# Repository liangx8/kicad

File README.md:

#content

  * esc ESC project
  * lib component package

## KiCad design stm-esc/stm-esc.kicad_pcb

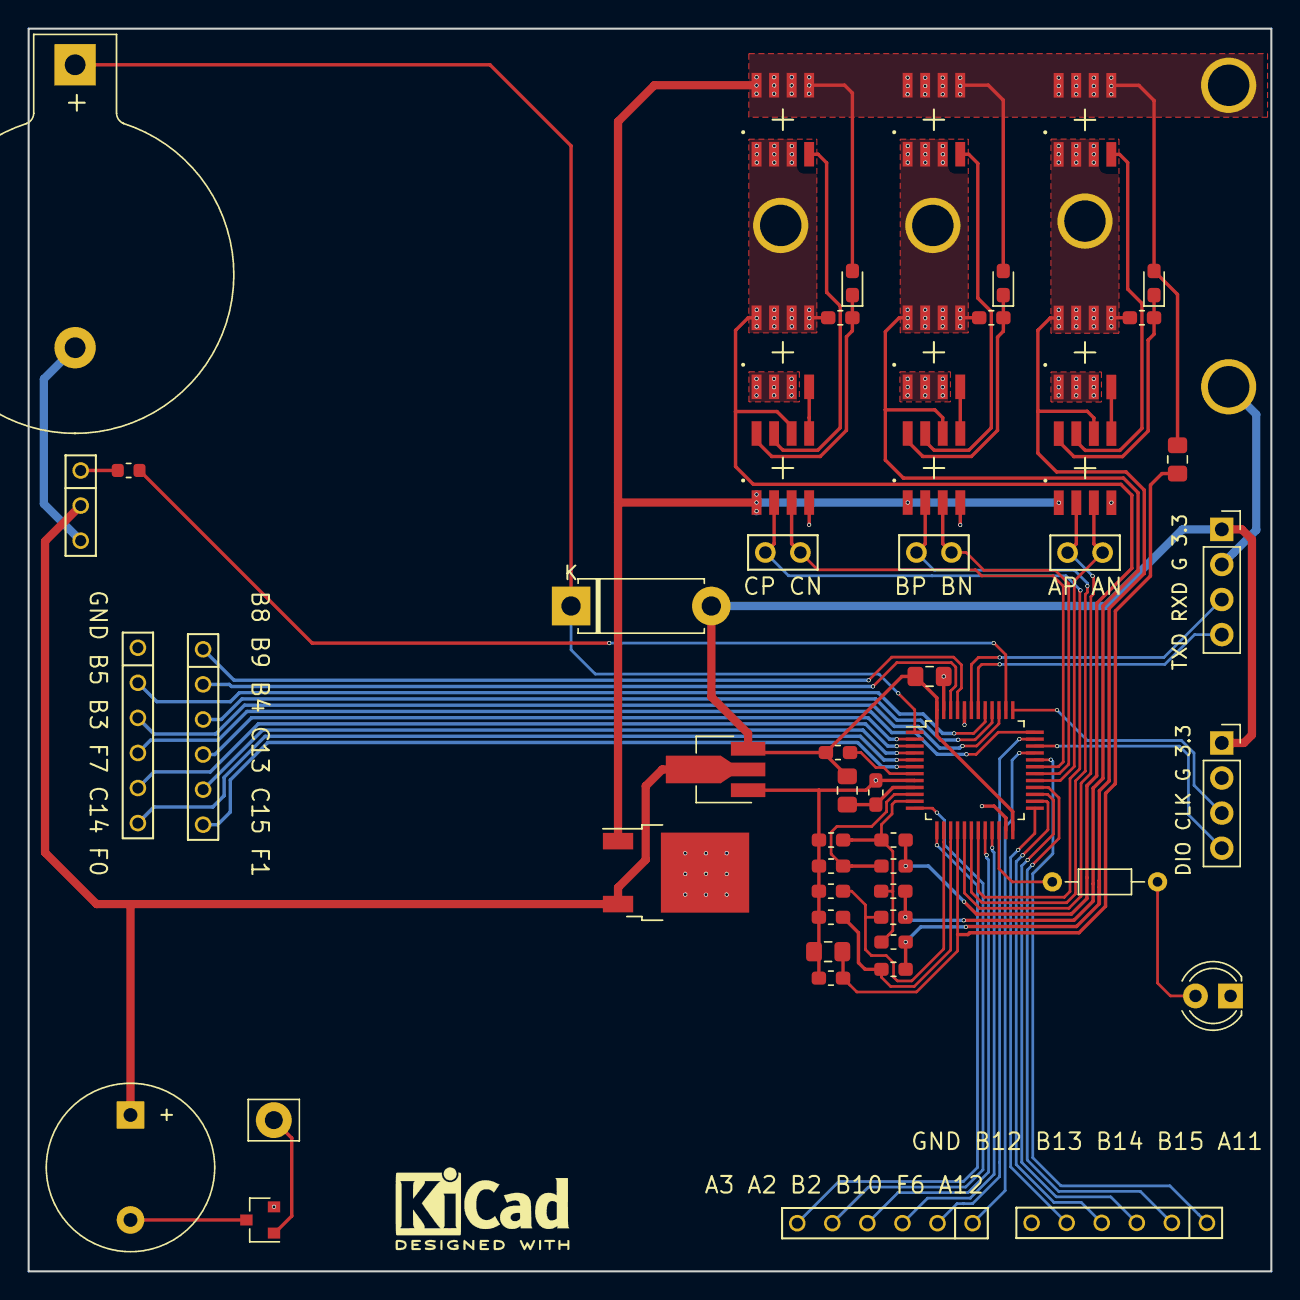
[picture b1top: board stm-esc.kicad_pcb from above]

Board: 2 copper layers, 90.0 x 90.0 mm, 58 parts (0 on the bottom side), 62 nets.

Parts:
BT1: Battery_Cell; BatteryHolder_Keystone_103_1x20mm
BZ1: Buzzer; Buzzer_12x9.5RM7.6
C1, C4: C; C_0603_1608Metric_Pad1.05x0.95mm_HandSolder
C2: C; C_0805_2012Metric_Pad1.15x1.40mm_HandSolder
C3: C; C_0603_1608Metric
C5: Ca; C_0603_1608Metric_Pad1.05x0.95mm_HandSolder
C6: Cc; C_0603_1608Metric_Pad1.05x0.95mm_HandSolder
C7: Cb; C_0603_1608Metric_Pad1.05x0.95mm_HandSolder
D1: D; D_5W_P10.16mm_Horizontal
D2: LED; LED_D4.0mm
D3: Da; D_0603_1608Metric_Pad1.05x0.95mm_HandSolder
D4: Dc; D_0603_1608Metric_Pad1.05x0.95mm_HandSolder
D5: Db; D_0603_1608Metric_Pad1.05x0.95mm_HandSolder
J1: A3 A2 B2 B10 F6 A12; conn-6x2.54mm
J2: GND B12 B13 B14 B15 A11; conn-6x2.54mm
J3, J4: Conn_01x06; conn-6x2.54mm
J5: Conn_01x01; Pin_D1.3mm_L10.0mm_W3.5mm_Flat
J6: DIO CLK G 3.3; PinSocket_1x04_P2.54mm_Vertical
J7: TXD RXD G 3.3; PinSocket_1x04_P2.54mm_Vertical
J8, J9, J14, J15, J16: Conn_01x01; HOLE-R1.5MM
J10: Conn_01x03; conn-3x2.54mm
J11: CP CN; SIP-2xP2.54mm
J12: BP BN; SIP-2xP2.54mm
J13: AP AN; SIP-2xP2.54mm
Q1: 2N7002; SOT-23
Q2, Q3, Q4, Q5, Q6, Q7: nfet; SOIC-8
R1, R13: 1k; R_0603_1608Metric_Pad1.05x0.95mm_HandSolder
R2: 1R; R_0805_2012Metric_Pad1.15x1.40mm_HandSolder
R3: 1K; R_Axial_DIN0204_L3.6mm_D1.6mm_P7.62mm_Horizontal
R4, R5: 2K; R_0805_2012Metric_Pad1.15x1.40mm_HandSolder
R6, R8, R10, R12, R14, R15: 20k; R_0603_1608Metric_Pad1.05x0.95mm_HandSolder
R7, R9, R11: 3k; R_0603_1608Metric_Pad1.05x0.95mm_HandSolder
U1: STM32F051C8Tx; LQFP-48_7x7mm_P0.5mm
U2: KA78M05_TO252; TO-252-2
U3: REGULAR-7133-1; SOT-89-3_Handsoldering
U4, U5, U6: IR2103; SOIC-8

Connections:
+3V3: C2.2, D1.2, J6.1, J7.1, R1.2, R2.1, U1.24, U1.48, U3.3
+5V: BZ1.1, J10.2, U2.3, U3.2
/LED: R3.2, U1.22
/PA2: J1.5, U1.12
/PA3: J1.6, U1.13
/PA11: J2.1, U1.32
/PA12: J1.1, U1.33
/PB2: J1.4, U1.20
/PB3: J3.3, U1.39
/PB4: J4.3, U1.40
/PB5: J3.2, U1.41
/PB8: J4.1, U1.45
/PB9: J4.2, U1.46
/PB10: J1.3, U1.21
/PB12: J2.5, U1.25
/PB13: J2.4, U1.26
/PB14: J2.3, U1.27
/PB15: J2.2, U1.28
/PC13: J4.4, U1.2
/PC14: J3.5, U1.3
/PC15: J4.5, U1.4
/PF0: J3.6, U1.5
/PF1: J4.6, U1.6
/PF6: J1.2, U1.35
/PF7: J3.4, U1.36
/Vdda: C1.2, R2.2, U1.9
/bridge a/AOUT: C5.2, J14.1, Q2.1, Q2.2, Q2.3, Q3.5, Q3.6, Q3.7, Q3.8, R10.1, R12.1, U4.6
/bridge b/BOUT: C7.2, J16.1, Q6.1, Q6.2, Q6.3, Q7.5, Q7.6, Q7.7, Q7.8, R8.1, R14.1, U6.6
/bridge c/COUT: C6.2, J15.1, Q4.1, Q4.2, Q4.3, Q5.5, Q5.6, Q5.7, Q5.8, R6.1, R15.1, U5.6
AN: J13.1, U1.29, U4.3
AP: J13.2, U1.17, U4.2
BN: J12.1, U1.30, U6.3
BP: J12.2, U1.18, U6.2
CN: J11.1, U1.31, U5.3
CP: J11.2, U1.19, U5.2
Fa: R10.2, R11.1, U1.15
Fabc: R12.2, R13.1, R14.2, R15.2, U1.11
Fb: R8.2, R9.1, U1.14
Fc: R6.2, R7.1, U1.10
GND: BT1.2, C1.1, C2.1, C4.2, D2.1, J2.6, J3.1, J6.2, J7.2, J9.1, J10.3, Q1.2, Q3.1, Q3.2, Q3.3, Q5.1, Q5.2, Q5.3, Q7.1, Q7.2, Q7.3, R5.2, R7.2, R9.2, R11.2, R13.2, U1.8, U1.23, U1.44, U1.47, U2.2, U3.1, U4.4, U5.4, U6.4
unnamed: BT1.1, D1.1, U1.1
unnamed: BZ1.2, Q1.3
unnamed: C3.1, J10.1
unnamed: C5.1, D3.1, U4.8
unnamed: C6.1, D4.1, U5.8
unnamed: C7.1, D5.1, U6.8
unnamed: D2.2, R3.1
unnamed: J5.1, Q1.1
unnamed: Q2.4, U4.7
unnamed: Q3.4, U4.5
unnamed: Q4.4, U5.7
unnamed: Q5.4, U5.5
unnamed: Q6.4, U6.7
unnamed: Q7.4, U6.5
unnamed: R1.1, U1.7
RCP: C3.2, U1.38
RXD: J7.3, U1.43
SWCLK: J6.3, U1.37
SWDIO: J6.4, U1.34
TXD: J7.4, U1.42
VCC: D3.2, D4.2, D5.2, J8.1, Q2.5, Q2.6, Q2.7, Q2.8, Q4.5, Q4.6, Q4.7, Q4.8, Q6.5, Q6.6, Q6.7, Q6.8, R4.1, U2.1, U4.1, U5.1, U6.1
V_SAMPLE: C4.1, R4.2, R5.1, U1.16

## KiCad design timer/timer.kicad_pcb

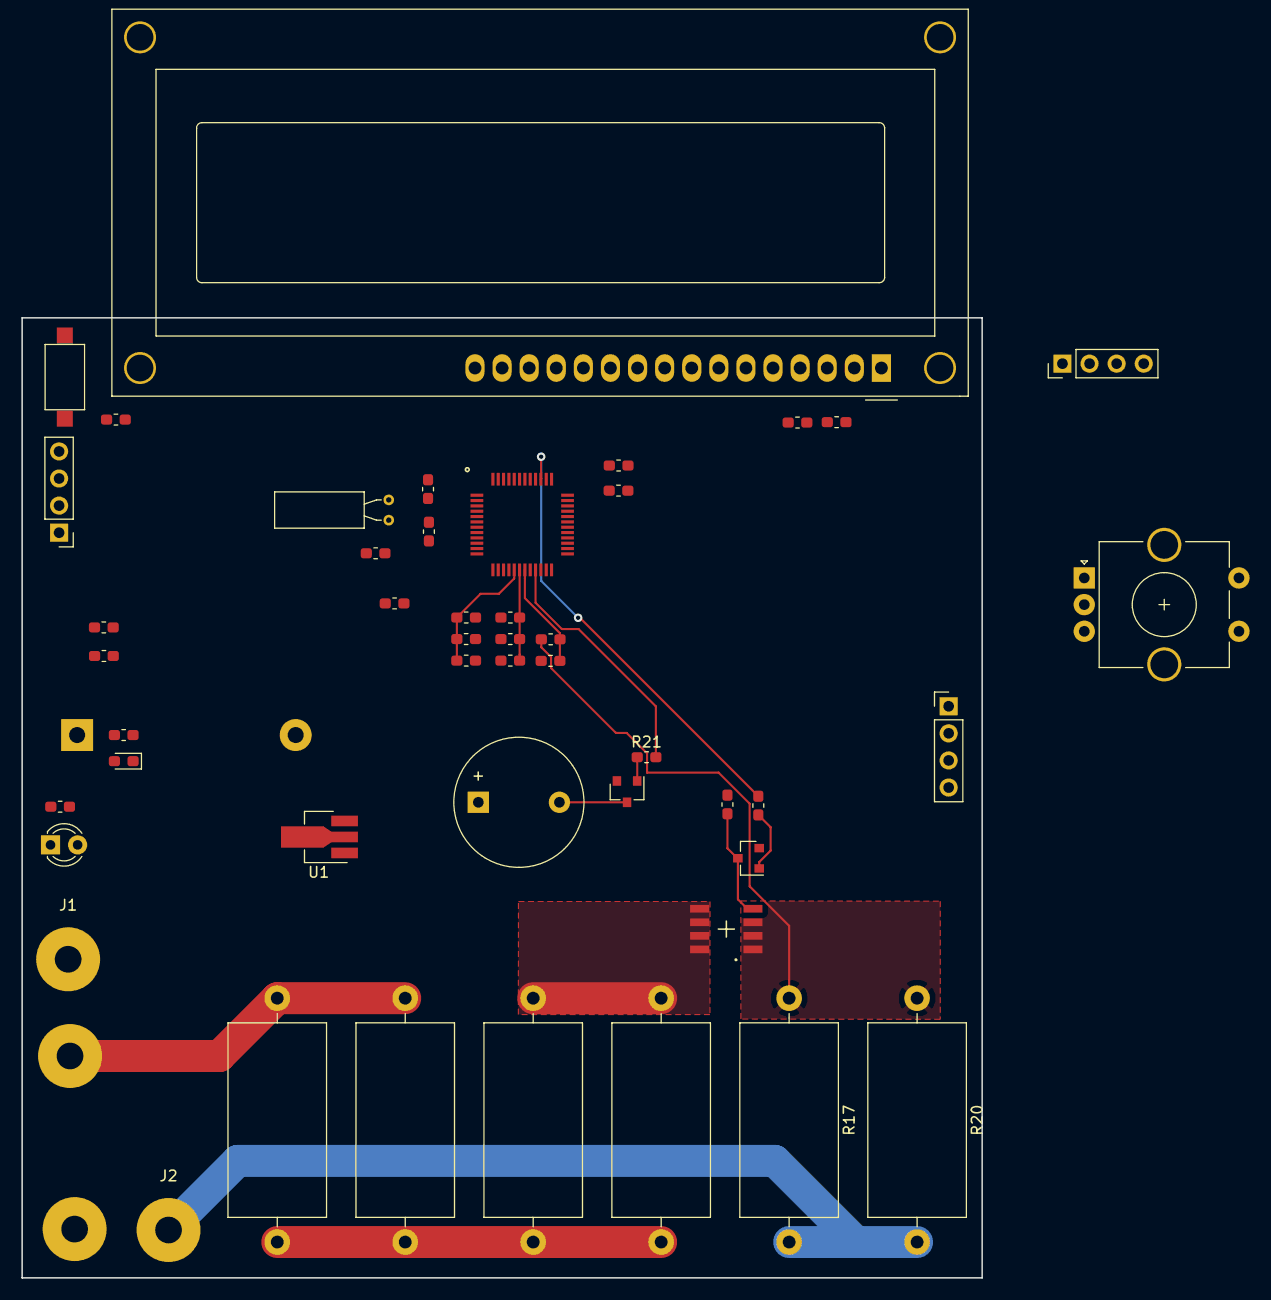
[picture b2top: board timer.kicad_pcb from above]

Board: 2 copper layers, 90.0 x 90.0 mm, 50 parts (1 on the bottom side), 40 nets.

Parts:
BZ1: Buzzer; Buzzer_12x9.5RM7.6
C1, C2: 20p; C_0603_1608Metric_Pad1.05x0.95mm_HandSolder
C3, C4, C5: Cpwr; C_0603_1608Metric_Pad1.05x0.95mm_HandSolder
C6: Calg; C_0603_1608Metric_Pad1.05x0.95mm_HandSolder
C7: Cvs; C_0603_1608Metric_Pad1.05x0.95mm_HandSolder
C8: Cbs; C_0603_1608Metric_Pad1.05x0.95mm_HandSolder
C9: Cis; C_0603_1608Metric_Pad1.05x0.95mm_HandSolder
D1: LED; LED_D3.0mm
D2: D; D_0603_1608Metric_Pad1.05x0.95mm_HandSolder
DS1: WC1602A
J1, J2, J7: Conn_01x01; SolderWirePad_1x01_Drill2.5mm
J3, J4, J5: Conn_01x04; PinHeader_1x04_P2.54mm_Vertical
J6: GND/B-; SolderWirePad_1x01_Drill2.5mm
J8: Conn_01x02; BatteryHolder_Keystone_104_1x23mm
Q1: Q_NPN_BEC; SOT-23
Q2: 2N7002; SOT-23
Q3: nfet; SOIC-8
R1, R2: R; R_0603_1608Metric_Pad1.05x0.95mm_HandSolder
R3: 3k; R_0603_1608Metric_Pad1.05x0.95mm_HandSolder
R4, R5, R12, R13, R21: 1k; R_0603_1608Metric_Pad1.05x0.95mm_HandSolder
R6, R7, R10, R11: 20K; R_0603_1608Metric_Pad1.05x0.95mm_HandSolder
R8: 47k; R_0603_1608Metric_Pad1.05x0.95mm_HandSolder
R9: 4.7k; R_0603_1608Metric_Pad1.05x0.95mm_HandSolder
R14: 10k; R_0603_1608Metric_Pad1.05x0.95mm_HandSolder
R15, R16, R17, R18, R19, R20: 0.1r; R_Axial_DIN0918_L18.0mm_D9.0mm_P22.86mm_Horizontal
SW1: Rotary_Encoder_Switch; RotaryEncoder_Alps_EC11E-Switch_Vertical_H20mm_CircularMoun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
SW2: SW_DIP_x01; SW_SPST_CK_RS282G05A3
U1: REGULAR-7133-1; SOT-89-3_Handsoldering
U2: STM32F103C8Tx; QFP_48_P0.5_W0.3
Y1: Crystal; Crystal_C38-LF_D3.0mm_L8.0mm_Horizontal

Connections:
+1V5: J8.1, R3.1, U2.1
+3V3: C3.1, C4.1, C5.1, C6.1, D2.2, DS1.2, J3.1, J4.1, J5.1, R2.2, R4.2, R5.2, R8.2, U1.3, U2.9, U2.24, U2.36, U2.48
/RESET: R2.1, SW2.2, U2.7
/RXD: J3.4, U2.31
/SWCLK: J4.4, U2.37
/SWDIO: J4.3, U2.34
/TXD: J3.3, U2.30
B+: J7.1, R10.1, R15.1, R18.1
Beep: R21.2, U2.21
Discharge: R12.2, U2.39
GND: C1.2, C2.1, C3.2, C4.2, C5.2, C6.2, C7.2, C8.2, C9.2, DS1.1, J2.1, J3.2, J4.2, J5.2, J6.1, J8.2, Q1.2, Q2.2, R1.2, R7.2, R9.1, R11.2, R17.2, R20.2, SW1.C, SW1.S2, SW2.1, U1.1, U2.8, U2.23, U2.35, U2.44, U2.47
IIC_SCL: J5.3, R4.1, U2.42
IIC_SDA: J5.4, R5.1, U2.43
Isample: C9.1, R14.2, U2.19
unnamed: BZ1.2, Q2.3
unnamed: C1.1, U2.3, Y1.1
unnamed: C2.2, U2.4, Y1.2
unnamed: D1.1, R1.1
unnamed: D1.2, U2.46
unnamed: D2.1, R3.2
unnamed: DS1.3, R8.1, R9.2
unnamed: DS1.4, U2.14
unnamed: DS1.5, U2.15
unnamed: DS1.6, U2.16
unnamed: DS1.11, U2.10
unnamed: DS1.12, U2.11
unnamed: DS1.13, U2.12
unnamed: DS1.14, U2.13
unnamed: Q1.1, R12.1
unnamed: Q1.3, Q3.4, R13.2
unnamed: Q2.1, R21.1
unnamed: Q3.1, Q3.2, Q3.3, R14.1, R17.1, R20.1
unnamed: Q3.5, Q3.6, Q3.7, Q3.8, R16.2, R19.2
unnamed: R15.2, R16.1, R18.2, R19.1
unnamed: SW1.A, U2.40
unnamed: SW1.B, U2.41
unnamed: SW1.S1, U2.45
VCC: BZ1.1, J1.1, R6.1, R13.1, U1.2
Vdd_sample: C7.1, R6.2, R7.1, U2.18
Vsample: C8.1, R10.2, R11.1, U2.17

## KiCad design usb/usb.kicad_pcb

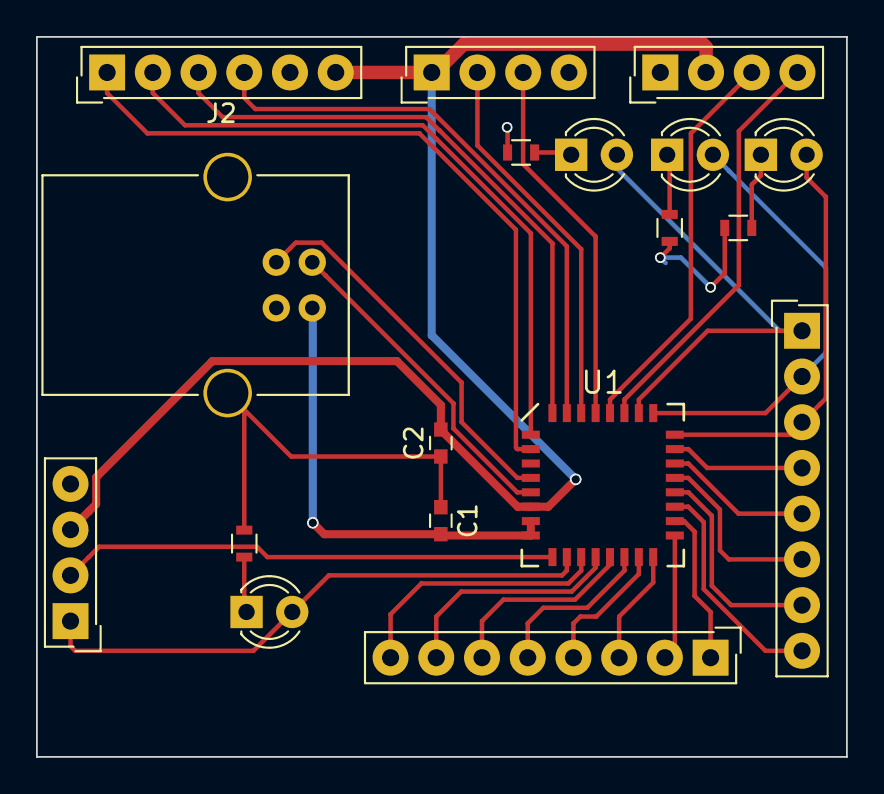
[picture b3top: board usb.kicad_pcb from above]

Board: 2 copper layers, 45.0 x 40.0 mm, 18 parts (0 on the bottom side), 35 nets.

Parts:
C1, C2: 4.7uF; C_0603
D1, D2, D3, D4: LED; LED_D3.0mm
J1: USB_B
J2: SPI; SL-106-X-XX_1x06
J3: C2 interface; SL-104-X-XX_1x04
J4: UART; SL-104-X-XX_1x04
J5: TWI; SL-104-X-XX_1x04
J6: GPIO1; SL-108-X-XX_1x08
J7: GPIO2; SL-108-X-XX_1x08
R1, R2, R3, R4: 1K; R_0603
U1: C8051F320; LQFP_32

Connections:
+3V3: C2.2, J2.6, J3.3, J4.1, J5.2, U1.6
/C2CK: J3.2, U1.9
/C2D: D1.2, J3.1, U1.10
/D+: J1.3, U1.4
/D-: J1.2, U1.5
/RXD: J4.3, U1.29
/TXD: J4.2, U1.30
/Vbus: C1.2, J1.1, U1.7, U1.8
GND: C1.1, C2.1, J1.4, J1.5, J2.5, J3.4, J4.4, J5.1, R1.2, R2.1, R3.1, R4.1, U1.3
unnamed: D1.1, R1.1
unnamed: D2.1, R2.2
unnamed: D2.2, J6.3, U1.24
unnamed: D3.1, R3.2
unnamed: D3.2, J6.2, U1.25
unnamed: D4.1, R4.2
unnamed: D4.2, J6.1, U1.26
unnamed: J2.1, U1.2
unnamed: J2.2, U1.1
unnamed: J2.3, U1.32
unnamed: J2.4, U1.31
unnamed: J5.3, U1.28
unnamed: J5.4, U1.27
unnamed: J6.4, U1.23
unnamed: J6.5, U1.22
unnamed: J6.6, U1.21
unnamed: J6.7, U1.20
unnamed: J6.8, U1.19
unnamed: J7.1, U1.18
unnamed: J7.2, U1.17
unnamed: J7.3, U1.16
unnamed: J7.4, U1.15
unnamed: J7.5, U1.14
unnamed: J7.6, U1.13
unnamed: J7.7, U1.12
unnamed: J7.8, U1.11

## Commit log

2017-05-17 startup
2017-05-17 pause work
2017-05-17 temp
2017-05-18 usb project
2017-05-18 usb experiement
2017-05-26 improve usb board
2017-07-01 add stm32 esc
2017-08-12 stm32 esc project
2017-08-12 stm003 sch
2018-03-23 work at home
2018-03-25 almost done for stm-esc
2018-03-29 improve
2018-03-30 定板打样stm-esc
2018-04-21 change pcb.py
2018-05-01 add stm32f103-core component
2018-05-29 stm-esc 48pin mcu 定板打样
2018-06-04 minor change for stm-esc
2018-06-07 correct pin define for regular v3.3
2018-07-28 add footprints.sh for install footprints to local
2018-08-09 project timer
2018-11-04 working
2018-11-09 定板打样，单片机的退偶电容完整，数字电源和模拟电源隔离
2021-03-15 new component
2021-03-17 add 3D model to QFP48
2021-03-17 add PinHeader
2021-03-18 maniplate retangular zone
2022-01-10 update component to kicad 6
2022-04-09 qfn20
2022-05-05 pcbnew api was changed
2023-09-28 plugin for pcbnew
